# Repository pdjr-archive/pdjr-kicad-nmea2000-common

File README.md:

# pdjr-kicad-nmea2000-common

This project provides a circuit design and PCB layout for the generic
elements of an NMEA 2000 module based around the Teensy 4.0
microcontroller.

The PCB layout can be imported into other projects, relieving them of
the effort of designing and implementing fundamental services which
power, interface, configure and process most NMEA hardware devices.
A project designer using the PCB layout can focus on just those
elements of application design appropriate to their task in hand.

A parallel project
[pdjr-nmea2000-common-firmware]()
provides a C++ pattern and associated libraries that can be used as
a basis for implementing firmware which exploits this hardware.

## Design elements

### PCB

The double-sided PCB is suitable for use in a *** case and employs
both surface-mount and through-hole components.

### Microcontroller

The project supports both Teensy 3.2 and Teensy 4.0 microcontroller
modules.

### Power supply

A TMR-2-2411 DC-DC converter takes bus power from NET-S/NET-C and
outputs a 5VDC 400mA supply for the PCB.

The converter power supply input is protected by a 0.25A
self-resetting polymer fuse selected on the assumption of a 12VDC
bus voltage.

Output from the converter is filtered through a smooting capacitor.

### CAN interface

An MCP-2551/IP CAN controller converts data on CAN-H/CAN-L to 5VDC
signals suitable for microcontroller use. Provision is made for the
inclusion of a switch-selectable 120 Ohm bus termination resistor.
Microocontroller connections are level shifted to 3.3V

### Configuration interface

The configuration interface consists of an SPST momentary tactile
switch (PRG) and an 8-position DIL switch (INSTANCE).

PRG is directly connected to GPIO D14 and is active low (GPIO D14
should be configured with INPUT_PULLUP).

INSTANCE channels are pulled low to 3.3V and connected to the
parallel inputs of a PISO buffer with the buffer interface connected
to GPIO D10, D11 and D12.

### Display interface

The display interface consists of a single TRANSMIT_LED and up to 16
additional LEDs that can be used for the presentation of application
specific status.

TRANSMIT_LED is driven directly by GPIO D15.

The status LEDs are driven at 5VDC by a SIPO buffer with the buffer
interface connected to GPIO D0, D1 and D2.
   
## How to use this PCB design as the basis for a new project

The PCB design is simply imported into a new KiCad project and then
extended to provide the required application features.

1. Open Kicad(1) and create a new project.

2. Download MNEA2000-COMMON.kicad_pcb into the new project folder.

3. Open pcbnew(1), choose FILE->MERGE, select the file you just
   downloaded and save it as a the new project's PCB (if your KiCad
   project is called blob.prj then save the file as blob.kicad_pcb).
   
4.

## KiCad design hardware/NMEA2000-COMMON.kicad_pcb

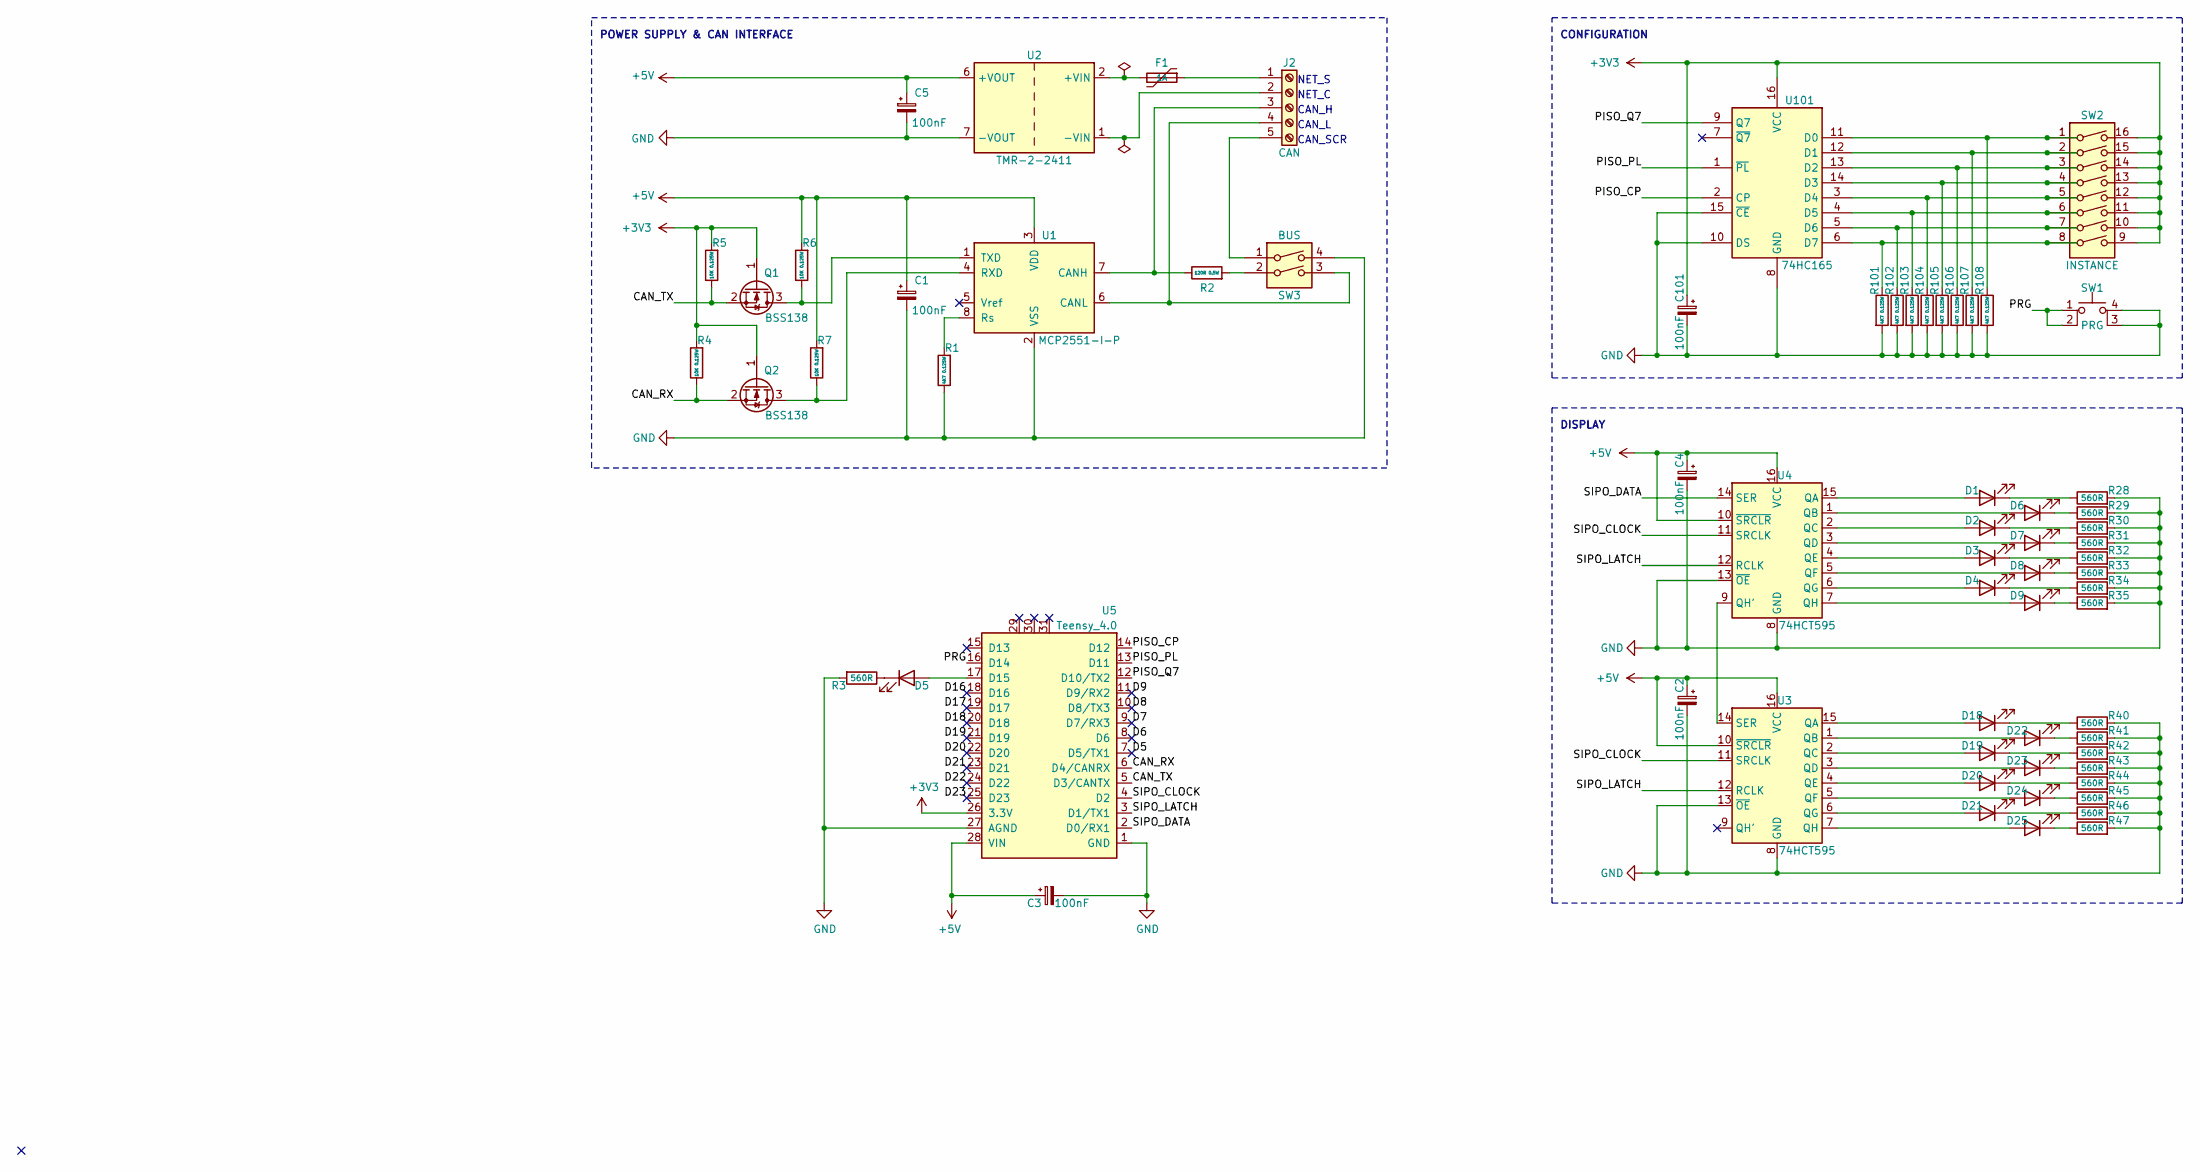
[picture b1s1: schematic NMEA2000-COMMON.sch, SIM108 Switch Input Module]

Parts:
C1, C2, C3, C4, C101: 100nF; C_0805_2012Metric
C5: 100nF; CP_Radial_D5.0mm_P2.50mm
D1, D2, D3, D4, D5, D6, D7, D8, D9, D18, D19, D20, D21, D22, D23, D24, D25: LED; LED_D1.8mm_W3.3mm_H2.4mm
F1: 1A; Fuse_Littelfuse_395Series
J2: CAN; PinHeader_1x05_P2.54mm_Vertical
Q1, Q2: BSS138; SOT-23
R1, R101, R102, R103, R104, R105, R106, R107, R108: 4K7 0.125W; R_0805_2012Metric
R2: 120R 0.5W; R_Axial_DIN0207_L6.3mm_D2.5mm_P7.62mm_Horizontal
R3, R28, R29, R30, R31, R32, R33, R34, R35, R40, R41, R42, R43, R44, R45, R46, R47: 560R; R_0805_2012Metric
R4, R5, R6, R7: 10K 0.125W; R_0805_2012Metric
SW1: PRG; SW_TH_Tactile_Omron_B3F-10xx
SW2: INSTANCE; DIP-16_W7.62mm
SW3: BUS; DIP-4_W7.62mm_LongPads
U1: MCP2551-I-P; SOIC-8_3.9x4.9mm_P1.27mm
U2: TMR-2-2411; TMR_2411
U3, U4: 74HCT595; SO-16_3.9x9.9mm_P1.27mm
U5: Teensy_4.0; DIP-28_W15.24mm_LongPads
U101: 74HC165; SO-16_3.9x9.9mm_P1.27mm

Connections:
+3V3: C101.1, Q1.1 (G), Q2.1 (G), R4.2, R5.2, SW2.9, SW2.10, SW2.11, SW2.12, SW2.13, SW2.14, SW2.15, SW2.16, U5.26 (3.3V), U101.16 (VCC); also elsewhere on the board
+5V: C1.1, C2.1, C3.1, C4.1, C5.1, R6.2, R7.2, U1.3 (VDD), U2.6 (+VOUT), U3.10 (~SRCLR), U3.16 (VCC), U4.10 (~SRCLR), U4.16 (VCC), U5.28 (VIN); also elsewhere on the board
/CAN_RX: Q2.2 (S), R4.1, U5.6 (D4/CANRX)
/CAN_TX: Q1.2 (S), R5.1, U5.5 (D3/CANTX)
/D5: U5.7 (D5/TX1)
/D6: U5.8 (D6)
/D7: U5.9 (D7/RX3)
/D8: U5.10 (D8/TX3)
/D9: U5.11 (D9/RX2)
/D16: U5.18 (D16)
/D17: U5.19 (D17)
/D18: U5.20 (D18)
/D19: U5.21 (D19)
/D20: U5.22 (D20)
/D21: U5.23 (D21)
/D22: U5.24 (D22)
/D23: U5.25 (D23)
/PISO_CP: U5.14 (D12), U101.2 (CP)
/PISO_PL: U5.13 (D11), U101.1 (~PL)
/PISO_Q7: U5.12 (D10/TX2), U101.9 (Q7)
/PRG: SW1.1, SW1.2, U5.16 (D14)
/SIPO_CLOCK: U3.11 (SRCLK), U4.11 (SRCLK), U5.4 (D2)
/SIPO_DATA: U4.14 (SER), U5.2 (D0/RX1)
/SIPO_LATCH: U3.12 (RCLK), U4.12 (RCLK), U5.3 (D1/TX1)
GND: C1.2, C2.2, C3.2, C4.2, C5.2, C101.2, R1.1, R3.2, R28.2, R29.2, R30.2, R31.2, R32.2, R33.2, R34.2, R35.2, R40.2, R41.2, R42.2, R43.2, R44.2, R45.2, R46.2, R47.2, R101.2, R102.2, R103.2, R104.2, R105.2, R106.2, R107.2, R108.2, SW1.3 (K), SW1.4 (A), SW3.4, U1.2 (VSS), U2.7 (-VOUT), U3.8 (GND), U3.13 (~OE), U4.8 (GND), U4.13 (~OE), U5.1 (GND), U5.27 (AGND), U101.8 (GND), U101.10 (DS), U101.15 (~CE)
unnamed: D1.1 (K), R28.1
unnamed: D1.2 (A), U4.15 (QA)
unnamed: D2.1 (K), R30.1
unnamed: D2.2 (A), U4.2 (QC)
unnamed: D3.1 (K), R32.1
unnamed: D3.2 (A), U4.4 (QE)
unnamed: D4.1 (K), R34.1
unnamed: D4.2 (A), U4.6 (QG)
unnamed: D5.1 (K), R3.1
unnamed: D5.2 (A), U5.17 (D15)
unnamed: D6.1 (K), R29.1
unnamed: D6.2 (A), U4.1 (QB)
unnamed: D7.1 (K), R31.1
unnamed: D7.2 (A), U4.3 (QD)
unnamed: D8.1 (K), R33.1
unnamed: D8.2 (A), U4.5 (QF)
unnamed: D9.1 (K), R35.1
unnamed: D9.2 (A), U4.7 (QH)
unnamed: D18.1 (K), R40.1
unnamed: D18.2 (A), U3.15 (QA)
unnamed: D19.1 (K), R42.1
unnamed: D19.2 (A), U3.2 (QC)
unnamed: D20.1 (K), R44.1
unnamed: D20.2 (A), U3.4 (QE)
unnamed: D21.1 (K), R46.1
unnamed: D21.2 (A), U3.6 (QG)
unnamed: D22.1 (K), R41.1
unnamed: D22.2 (A), U3.1 (QB)
unnamed: D23.1 (K), R43.1
unnamed: D23.2 (A), U3.3 (QD)
unnamed: D24.1 (K), R45.1
unnamed: D24.2 (A), U3.5 (QF)
unnamed: D25.1 (K), R47.1
unnamed: D25.2 (A), U3.7 (QH)
unnamed: F1.1, J2.1
unnamed: F1.2, U2.2 (+VIN)
unnamed: J2.2, U2.1 (-VIN)
unnamed: J2.3, R2.1, U1.7 (CANH)
unnamed: J2.4, SW3.3, U1.6 (CANL)
unnamed: J2.5, SW3.1
unnamed: Q1.3 (D), R6.1, U1.1 (TXD)
unnamed: Q2.3 (D), R7.1, U1.4 (RXD)
unnamed: R1.2, U1.8 (Rs)
unnamed: R2.2, SW3.2
unnamed: R101.1, SW2.8, U101.6 (D7)
unnamed: R102.1, SW2.7, U101.5 (D6)
unnamed: R103.1, SW2.6, U101.4 (D5)
unnamed: R104.1, SW2.5, U101.3 (D4)
unnamed: R105.1, SW2.4, U101.14 (D3)
unnamed: R106.1, SW2.3, U101.13 (D2)
unnamed: R107.1, SW2.2, U101.12 (D1)
unnamed: R108.1, SW2.1, U101.11 (D0)
unnamed: U3.14 (SER), U4.9 (QH')

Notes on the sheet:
POWER SUPPLY & CAN INTERFACE
NET_S
NET_C
CAN_H
CAN_L
CAN_SCR
CONFIGURATION
DISPLAY

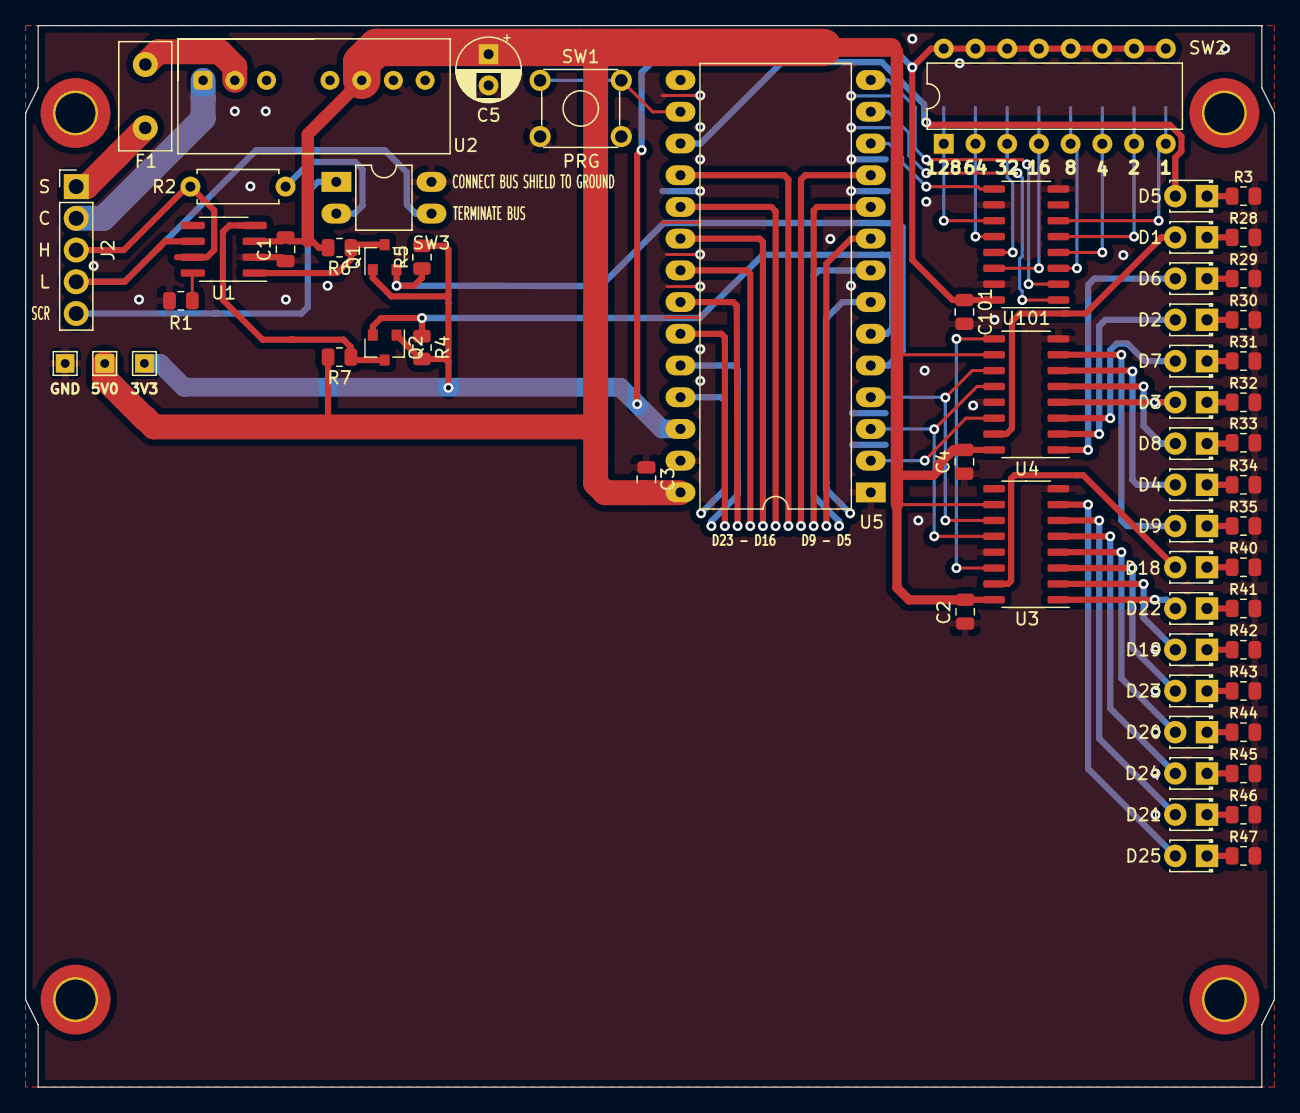
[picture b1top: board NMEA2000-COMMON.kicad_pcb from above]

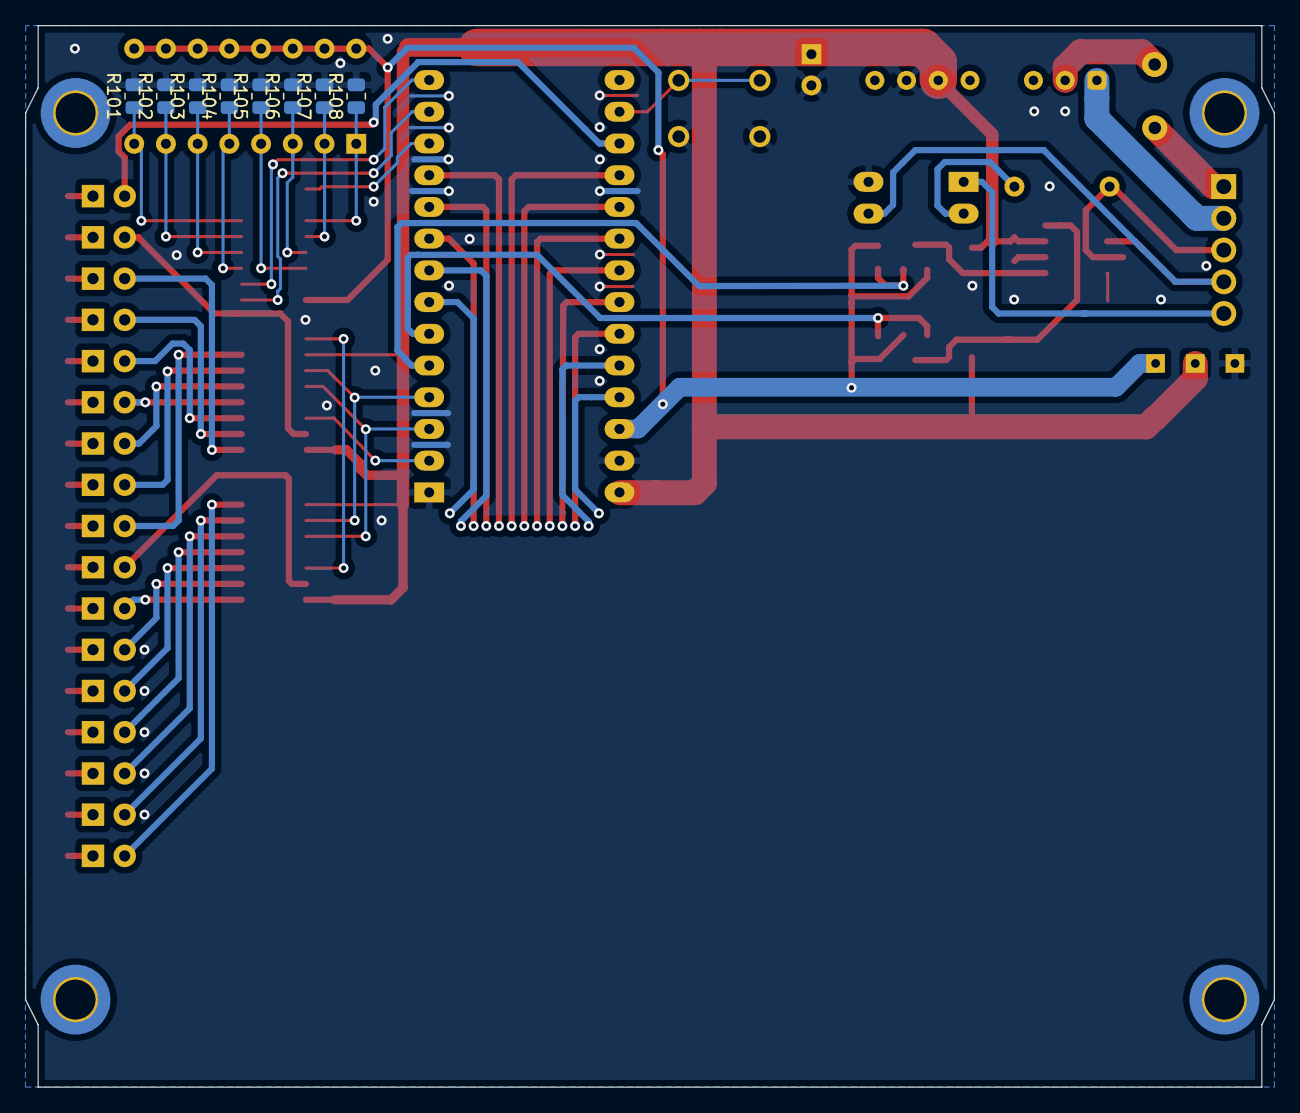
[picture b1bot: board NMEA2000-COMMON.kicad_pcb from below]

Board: 2 copper layers, 100.0 x 85.0 mm, 69 parts (8 on the bottom side), 65 nets.

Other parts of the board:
TEST 5V0, TEST 5V0#2: TestPoint_THTPad_1.5x1.5mm_Drill0.7mm

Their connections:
+3V3: TEST 5V0.1; also elsewhere on the board
+5V: TEST 5V0#2.1; also elsewhere on the board

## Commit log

2022-12-07 First upload
2022-12-07 Tweak
2022-12-07 Update library mappings
2022-12-08 Update silk layer.
2022-12-08 Update PRG switch position
2022-12-08 Rebuild
2022-12-08 Revise INSTANCE
2022-12-08 PISI update
2022-12-08 Tidy up
2022-12-09 Tidy up.
2022-12-09 Track resize
2022-12-09 Reroute
2022-12-10 Reroute PISO
2022-12-10 Add level shifters
2022-12-10 Drive PISO at 3.3V
2022-12-10 Revise logic shifter R values
2022-12-10 Move PISO to 3.3VDC
2022-12-10 Schematic tidy up
2022-12-10 Relay PCB
2022-12-10 Add expansion to SIPO LED
2022-12-11 Stuff
2022-12-11 Refactor
2022-12-20 Ground plane adjustments
2022-12-20 Relay
